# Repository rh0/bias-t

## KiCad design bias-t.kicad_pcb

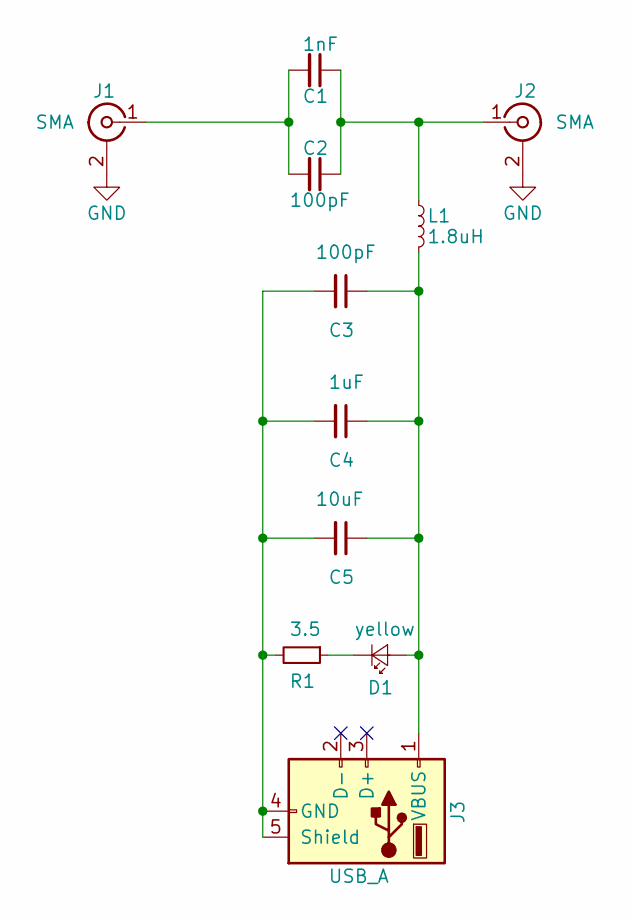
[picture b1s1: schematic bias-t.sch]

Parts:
C1: 1nF; C_0805_HandSoldering
C2, C3: 100pF; C_0805_HandSoldering
C4: 1uF; C_0805_HandSoldering
C5: 10uF; C_0805_HandSoldering
D1: yellow; LED_0805
J1, J2: SMA; SMA_SMD_Jack_Straight
J3: USB_A
L1: 1.8uH; Inductor_Taiyo-Yuden_NR-20xx_HandSoldering
R1: 3.5; R_0805

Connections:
GND: J1.2 (Ext), J2.2 (Ext)
unnamed: C1.1, C2.1, J2.1 (In), L1.1
unnamed: C1.2, C2.2, J1.1 (In)
unnamed: C3.1, C4.1, C5.1, D1.2 (A), J3.1 (VBUS), L1.2
unnamed: C3.2, C4.2, C5.2, J3.4 (GND), J3.5 (Shield), R1.2
unnamed: D1.1 (K), R1.1

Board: 2 copper layers, 11 parts (1 on the bottom side), 6 nets, no tracks yet.

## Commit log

2018-04-29 initial commit of bias t
